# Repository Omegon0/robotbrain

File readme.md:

# ROBOTBRAIN

An ESP32-based robot board that integrates two L293DD ICs to control four DC motor outputs. Also has an integrated magnetometer (LIS3MDL) for direction control. 

## Why? 

Last year for Science Olympiad's Robot Tour event, I designed an omnidirectional robot with tons of features, and importantly, many of them were based on QFN packages and a very weak LDO. 
This time I'm doing better. 5A LDO. No QFN (except the magnetometer). Proper power regulation. 
This will be the better robot. 

## What's changed? 

The previous version also contained a LSM6DSOX IC which has been scrapped since the SciOly robot can't effectively use linear and rotational acceleration data (too much drift). However magnetic field helps with absolute positioning. 
The previous version used a 1A LDO which was too little for three motors. This uses a 5A LDO which is plenty for 4 motors. The motor drivers have been upgraded to large L293DD packages to account for the higher current load. 
The power switching system has been significantly simplified, using a physical switch to alternate between battery power and USB power. There is no integrated battery charging since the robot is designed to use 8xAA (12V) instead of a 3.7V LiPo. 
Has an extra button to calibrate and start the robot because it may be easier than resetting. can be used to toggle on/off instead of robot running every time code uploads. 

## Images

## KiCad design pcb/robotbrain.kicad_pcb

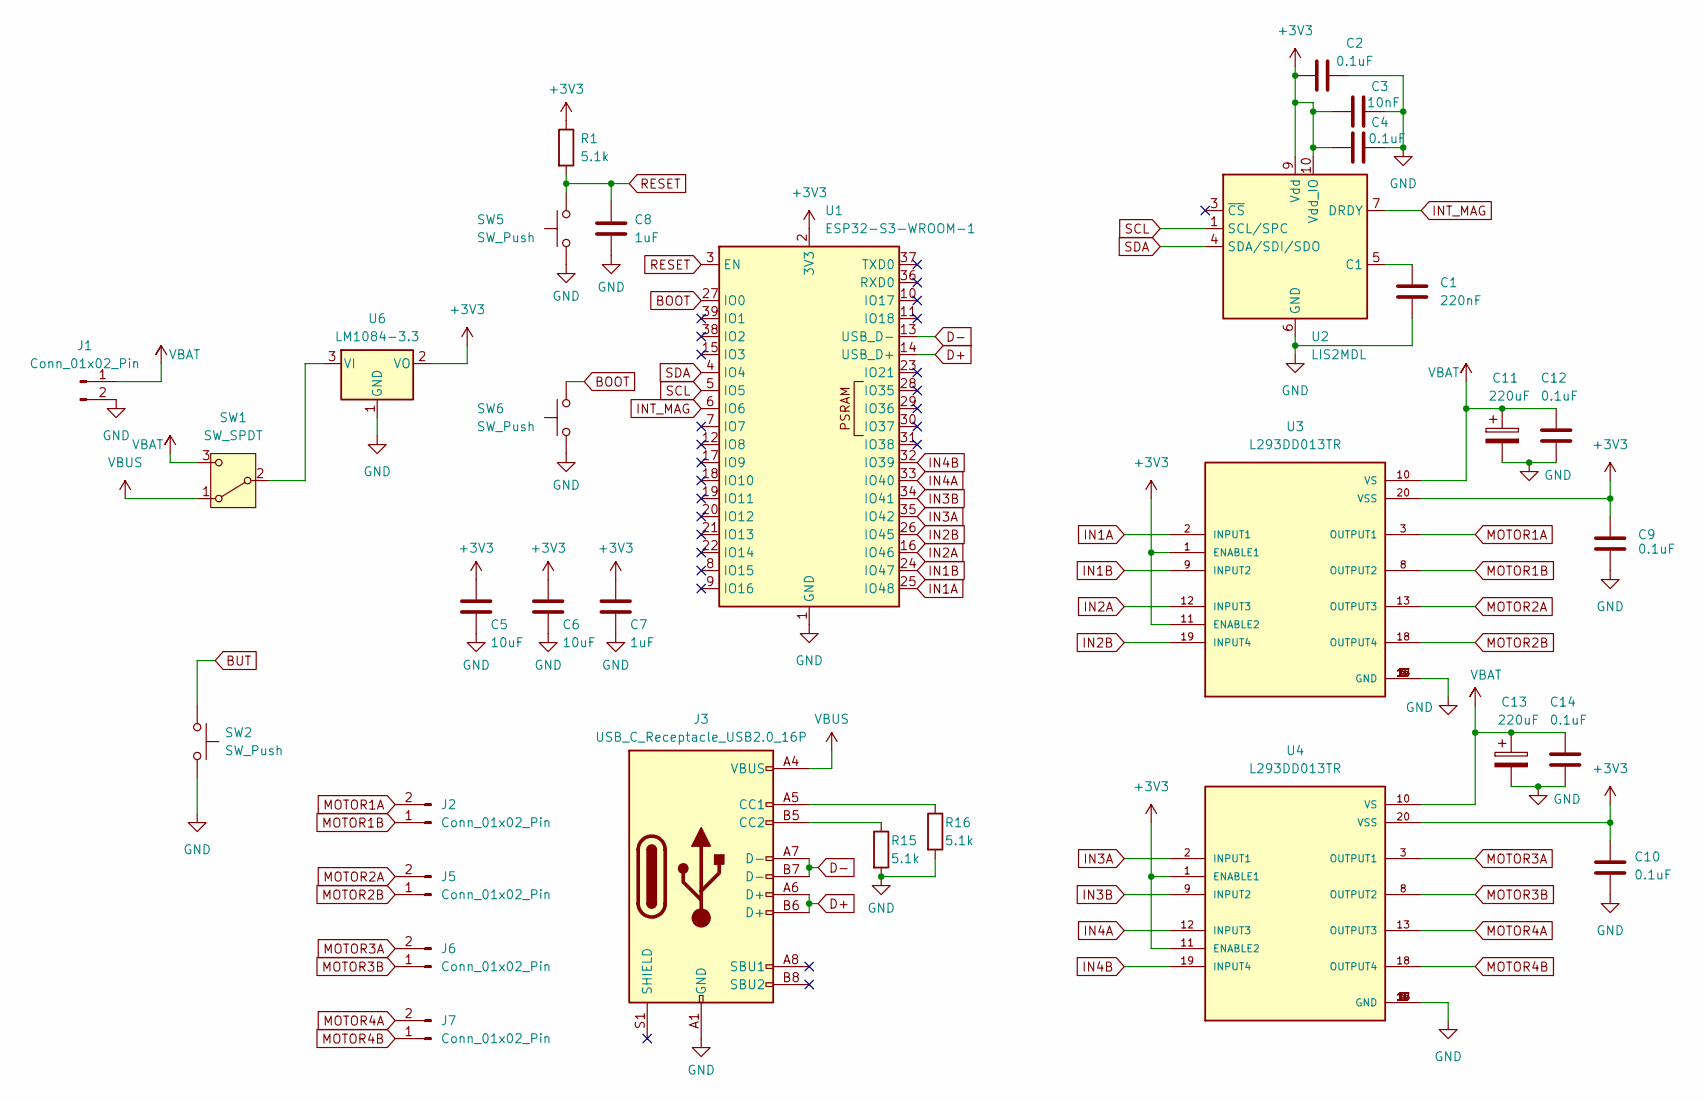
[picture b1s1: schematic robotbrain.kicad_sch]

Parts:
C1: 220nF; C_0805_2012Metric
C2, C4, C9, C10, C12, C14: 0.1uF; C_0805_2012Metric
C3: 10nF; C_0805_2012Metric
C5, C6: 10uF; C_0805_2012Metric
C7, C8: 1uF; C_0805_2012Metric
C11, C13: 220uF; CP_Radial_D10.0mm_P5.00mm
J1, J2, J5, J6, J7: Conn_01x02_Pin; PinHeader_1x02_P2.54mm_Vertical
J3: USB_C_Receptacle_USB2.0_16P; USB_C_Receptacle_GCT_USB4085
R1, R15, R16: 5.1k; R_0805_2012Metric
SW1: SW_SPDT; SS-12D10G5_XKB
SW2, SW5, SW6: SW_Push; SW_Push_1P1T_NO_CK_KSC6xxJ
U1: ESP32-S3-WROOM-1
U2: LIS2MDL; LGA-12_2x2mm_P0.5mm
U3, U4: L293DD013TR; SOIC127P1032X265-20N
U6: LM1084-3.3; TO254P1524X483-4N

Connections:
+3V3: C2.1, C3.1, C4.1, C5.1, C6.1, C7.1, C9.1, C10.1, R1.1, U1.2 (3V3), U2.9 (Vdd), U2.10 (Vdd_IO), U3.1 (ENABLE1), U3.11 (ENABLE2), U3.20 (VSS), U4.1 (ENABLE1), U4.11 (ENABLE2), U4.20 (VSS), U6.2 (VO)
BOOT: SW6.2, U1.27 (IO0)
BUT: SW2.1
D+: J3.A6 (D+), J3.B6 (D+), U1.14 (USB_D+)
D-: J3.A7 (D-), J3.B7 (D-), U1.13 (USB_D-)
GND: C1.2, C2.2, C3.2, C4.2, C5.2, C6.2, C7.2, C8.2, C9.2, C10.2, C11.2, C12.2, C13.2, C14.2, J1.2, J3.A1 (GND), J3.A12 (GND), J3.B1 (GND), J3.B12 (GND), R15.2, R16.2, SW2.2, SW5.1, SW6.1, U1.1 (GND), U1.40 (GND), U1.41 (GND), U2.6 (GND), U2.8 (GND), U3.4 (GND), U3.5 (GND), U3.6 (GND), U3.7 (GND), U3.14 (GND), U3.15 (GND), U3.16 (GND), U3.17 (GND), U4.4 (GND), U4.5 (GND), U4.6 (GND), U4.7 (GND), U4.14 (GND), U4.15 (GND), U4.16 (GND), U4.17 (GND), U6.1 (GND)
IN1A: U1.25 (IO48), U3.2 (INPUT1)
IN1B: U1.24 (IO47), U3.9 (INPUT2)
IN2A: U1.16 (IO46), U3.12 (INPUT3)
IN2B: U1.26 (IO45), U3.19 (INPUT4)
IN3A: U1.35 (IO42), U4.2 (INPUT1)
IN3B: U1.34 (IO41), U4.9 (INPUT2)
IN4A: U1.33 (IO40), U4.12 (INPUT3)
IN4B: U1.32 (IO39), U4.19 (INPUT4)
INT_MAG: U1.6 (IO6), U2.7 (DRDY)
MOTOR1A: J2.2, U3.3 (OUTPUT1)
MOTOR1B: J2.1, U3.8 (OUTPUT2)
MOTOR2A: J5.2, U3.13 (OUTPUT3)
MOTOR2B: J5.1, U3.18 (OUTPUT4)
MOTOR3A: J6.2, U4.3 (OUTPUT1)
MOTOR3B: J6.1, U4.8 (OUTPUT2)
MOTOR4A: J7.2, U4.13 (OUTPUT3)
MOTOR4B: J7.1, U4.18 (OUTPUT4)
unnamed: J3.A5 (CC1), R16.1
unnamed: J3.B5 (CC2), R15.1
unnamed: SW1.2 (B), U6.3 (VI)
unnamed: C1.1, U2.5 (C1)
RESET: C8.1, R1.2, SW5.2, U1.3 (EN)
SCL: U1.5 (IO5), U2.1 (SCL/SPC)
SDA: U1.4 (IO4), U2.4 (SDA/SDI/SDO)
VBAT: C11.1, C12.1, C13.1, C14.1, J1.1, SW1.3 (C), U3.10 (VS), U4.10 (VS)
VBUS: J3.A4 (VBUS), J3.A9 (VBUS), J3.B4 (VBUS), J3.B9 (VBUS), SW1.1 (A)

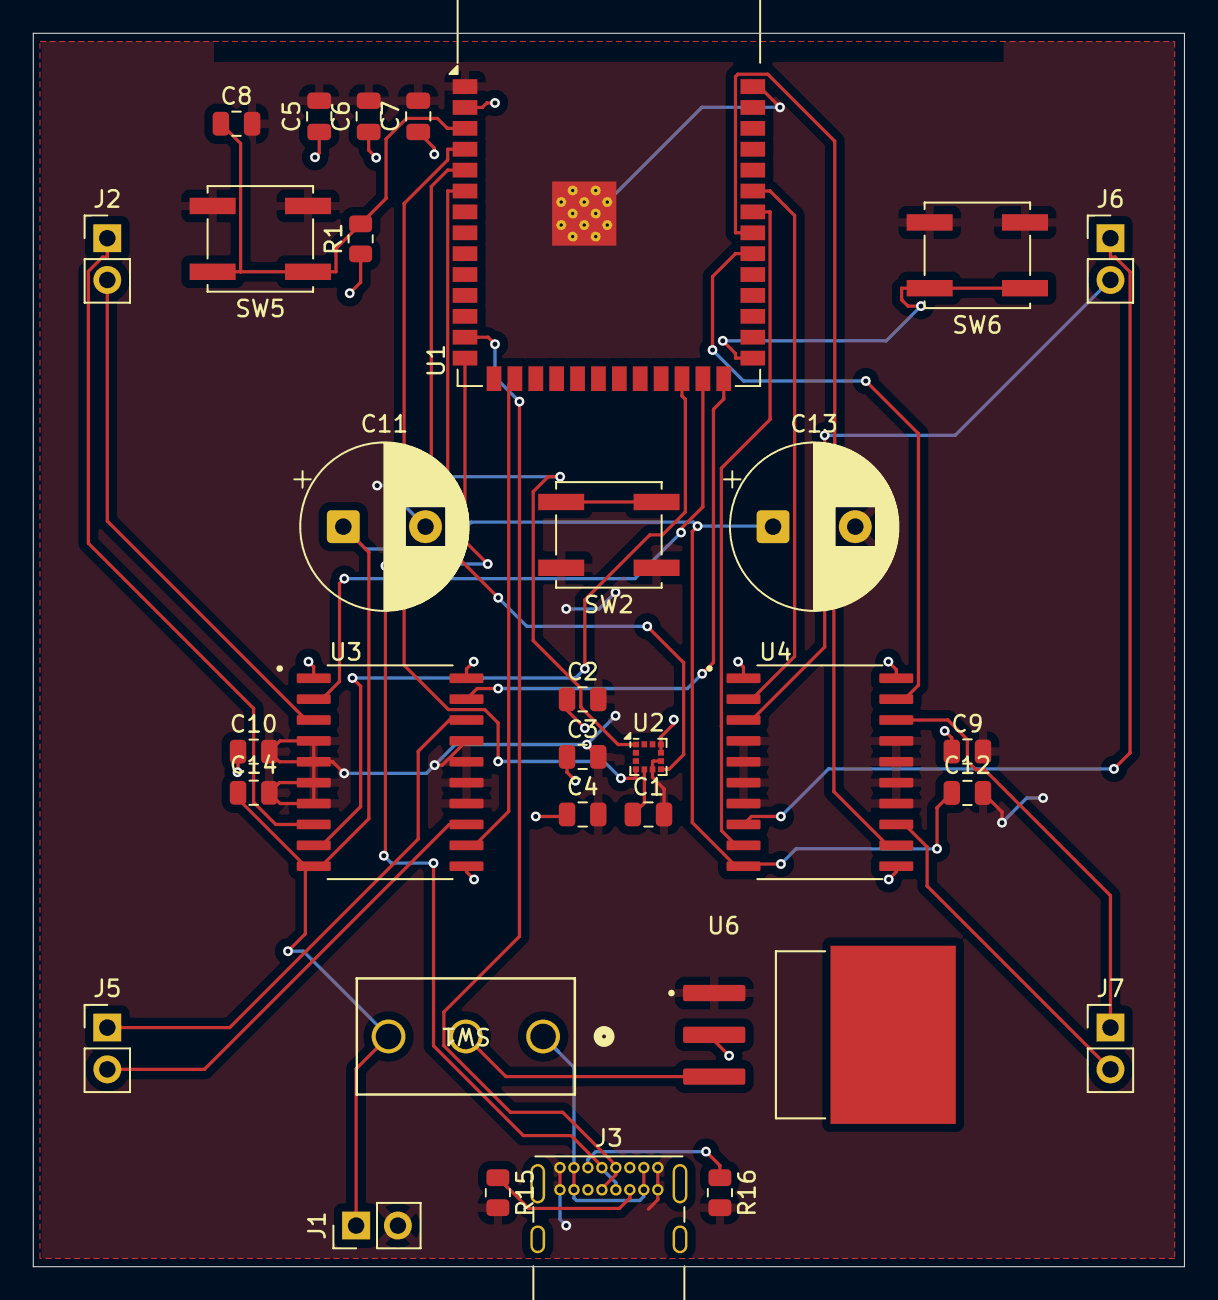
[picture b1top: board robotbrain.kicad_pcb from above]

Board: 2 copper layers, 70.0 x 75.0 mm, 32 parts (0 on the bottom side), 31 nets.

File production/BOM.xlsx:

Comment | Designator | Footprint | JLCPCB Part #（optional）
ST L293DD013TR | U3,U4 | SOIC127P1032X265-20N | C21610
ST LIS3MDLTR | U2 | LGA-12_2x2mm_P0.5mm | C478483
ESPRESSIF ESP32-S3-WROOM-1-N8 | U1 | ESP32-S3-WROOM-1 | C2913198
HGSEMI LM1084IS-3.3/TR | U6 | TO254P1524X483-4N | C19193518
220uF | C11,C13 | C_0805_2012Metric | C233093
220nF | C1 | C_0805_2012Metric | C48579621
100nF | C2,C4,C9,C10,C12,C14 | C_0805_2012Metric | C49326703
10nF | C3 | C_0805_2012Metric | C48579597
1uF | C7 | C_0805_2012Metric | C28323
10uF | C5,C6,C7 | C_0805_2012Metric | C48579582
USB C | J3 | USB_C_Receptacle_GCT_USB4085 | C7095263
SPDT | SW1 | SS-12D10G5_XKB | C319013
5.1k | R1,R15,R16 | R_0805_2012Metric | C27834

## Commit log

2025-08-19 dump everything
2025-08-19 added production files
